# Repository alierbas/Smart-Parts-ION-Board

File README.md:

# Smart Parts Ion Board 

This project is main board for Smart parts ion (Paintball marker)
  - Circuit is tested
  - Similar like original board
  - Open Hardware
  - The code is coming but you can write too. if you want.

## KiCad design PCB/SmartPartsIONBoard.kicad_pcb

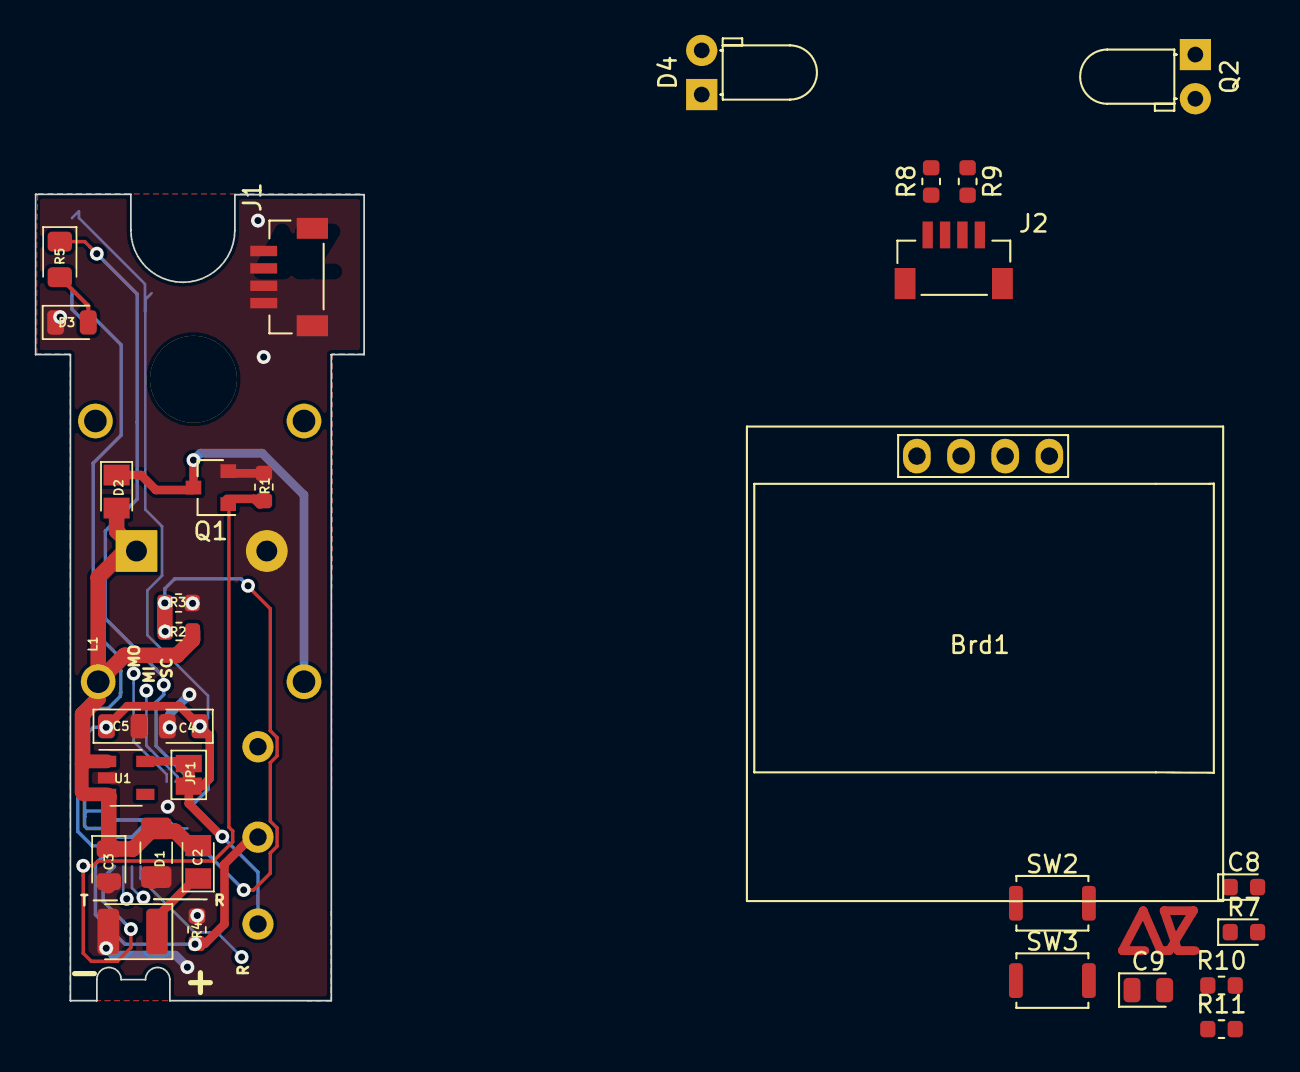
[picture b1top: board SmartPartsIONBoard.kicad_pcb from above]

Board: 2 copper layers, 18.9 x 46.4 mm, 37 parts (0 on the bottom side), 19 nets.

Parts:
BT1: Battery; LED_1210_3225Metric
Brd1: SSD1306; 128x64OLED
C1: 2200u; CP_Radial_D14.0mm_P7.50mm
C2: 10u; C_1206_3216Metric
C3, C4: 10u; LED_0805_2012Metric
C5, C9: 0.1u; LED_0805_2012Metric
C8: 0.1u; LED_0603_1608Metric
D1, D2: DIODE; D_MicroMELF
D3: LED; LED_0805_2012Metric
D4: LED_Small; LED_D3.0mm_Horizontal_O1.27mm_Z2.0mm_IRBlack
J1, J2: Conn_01x04; jst_4_smd
JP1: SolderJumper_2_Bridged; SolderJumper-2_P1.3mm_Bridged_Pad1.0x1.5mm
L1: L_Core_Ferrite; SmartPartsIonSelonoid
Q1: FDN337N; SOT-23
Q2: Q_Photo_NPN; LED_D3.0mm_Horizontal_O1.27mm_Z2.0mm_Clear
R1, R4: 1k; R_0603_1608Metric
R2, R3, R6, R10, R11: R_Small_US; R_0603_1608Metric
R5: 1k; LED_0805_2012Metric_Pad1.15x1.40mm_HandSolder
R7: 10k; LED_0603_1608Metric
R8: 100R; R_0603_1608Metric
R9: 10K; R_0603_1608Metric
SW1, SW2, SW3: SW_Push; SW_Push_SPST_NO_Alps_SKRK
U1: MIC5205-2.5YM5; SOT-23-5
U2: MAX313CPE; D2F_FL
U4: Logo-c; logo - c
U5: ATmega328P-MU; QFN-32-1EP_5x5mm_P0.5mm_EP3.1x3.1mm

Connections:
+9V: C1.1, C2.1, C3.1, D1.2, D2.2, L1.1, R2.1, U1.1, U1.3
A1: R2.2, R3.1, U5.24
A4: Brd1.3, U5.27
A5: Brd1.4, U5.28
D2: J1.3, Q1.1, R1.1, U5.32
D3: J1.2, R4.1, U2.2, U5.1
D4: R6.1, R10.1, R11.1, SW1.1, SW2.1, SW3.1, U5.2
GND: BT1.2, Brd1.1, C1.2, C2.2, C3.2, C4.2, C5.2, C9.2, D3.1, J1.4, J2.4, Q1.2, Q2.2, R1.2, R3.2, R4.2, R6.2, R10.2, R11.2, U1.2, U5.3, U5.5, U5.21, U5.33
unnamed: BT1.1, D1.1
unnamed: C9.1, U5.20
unnamed: D2.1, L1.2, Q1.3
unnamed: D3.2, R5.2
unnamed: D4.1, J2.2
unnamed: D4.2, R8.2
unnamed: J2.3, Q2.1, R9.2
unnamed: JP1.1, U1.5
RESET: C8.1, R7.2, U5.29
SCK: R5.1, U5.17
VCC: Brd1.2, C4.1, C5.1, J1.1, J2.1, JP1.2, R7.1, R8.1, R9.1, SW1.2, SW2.2, SW3.2, U2.3, U5.4, U5.6, U5.18

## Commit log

2020-04-09 inital
2020-04-09 First gerber, PCB Preview
2020-04-13 GND Fix
2020-08-11 Some results
2020-08-17 Eye And Oled Display
2020-08-28 some dev
